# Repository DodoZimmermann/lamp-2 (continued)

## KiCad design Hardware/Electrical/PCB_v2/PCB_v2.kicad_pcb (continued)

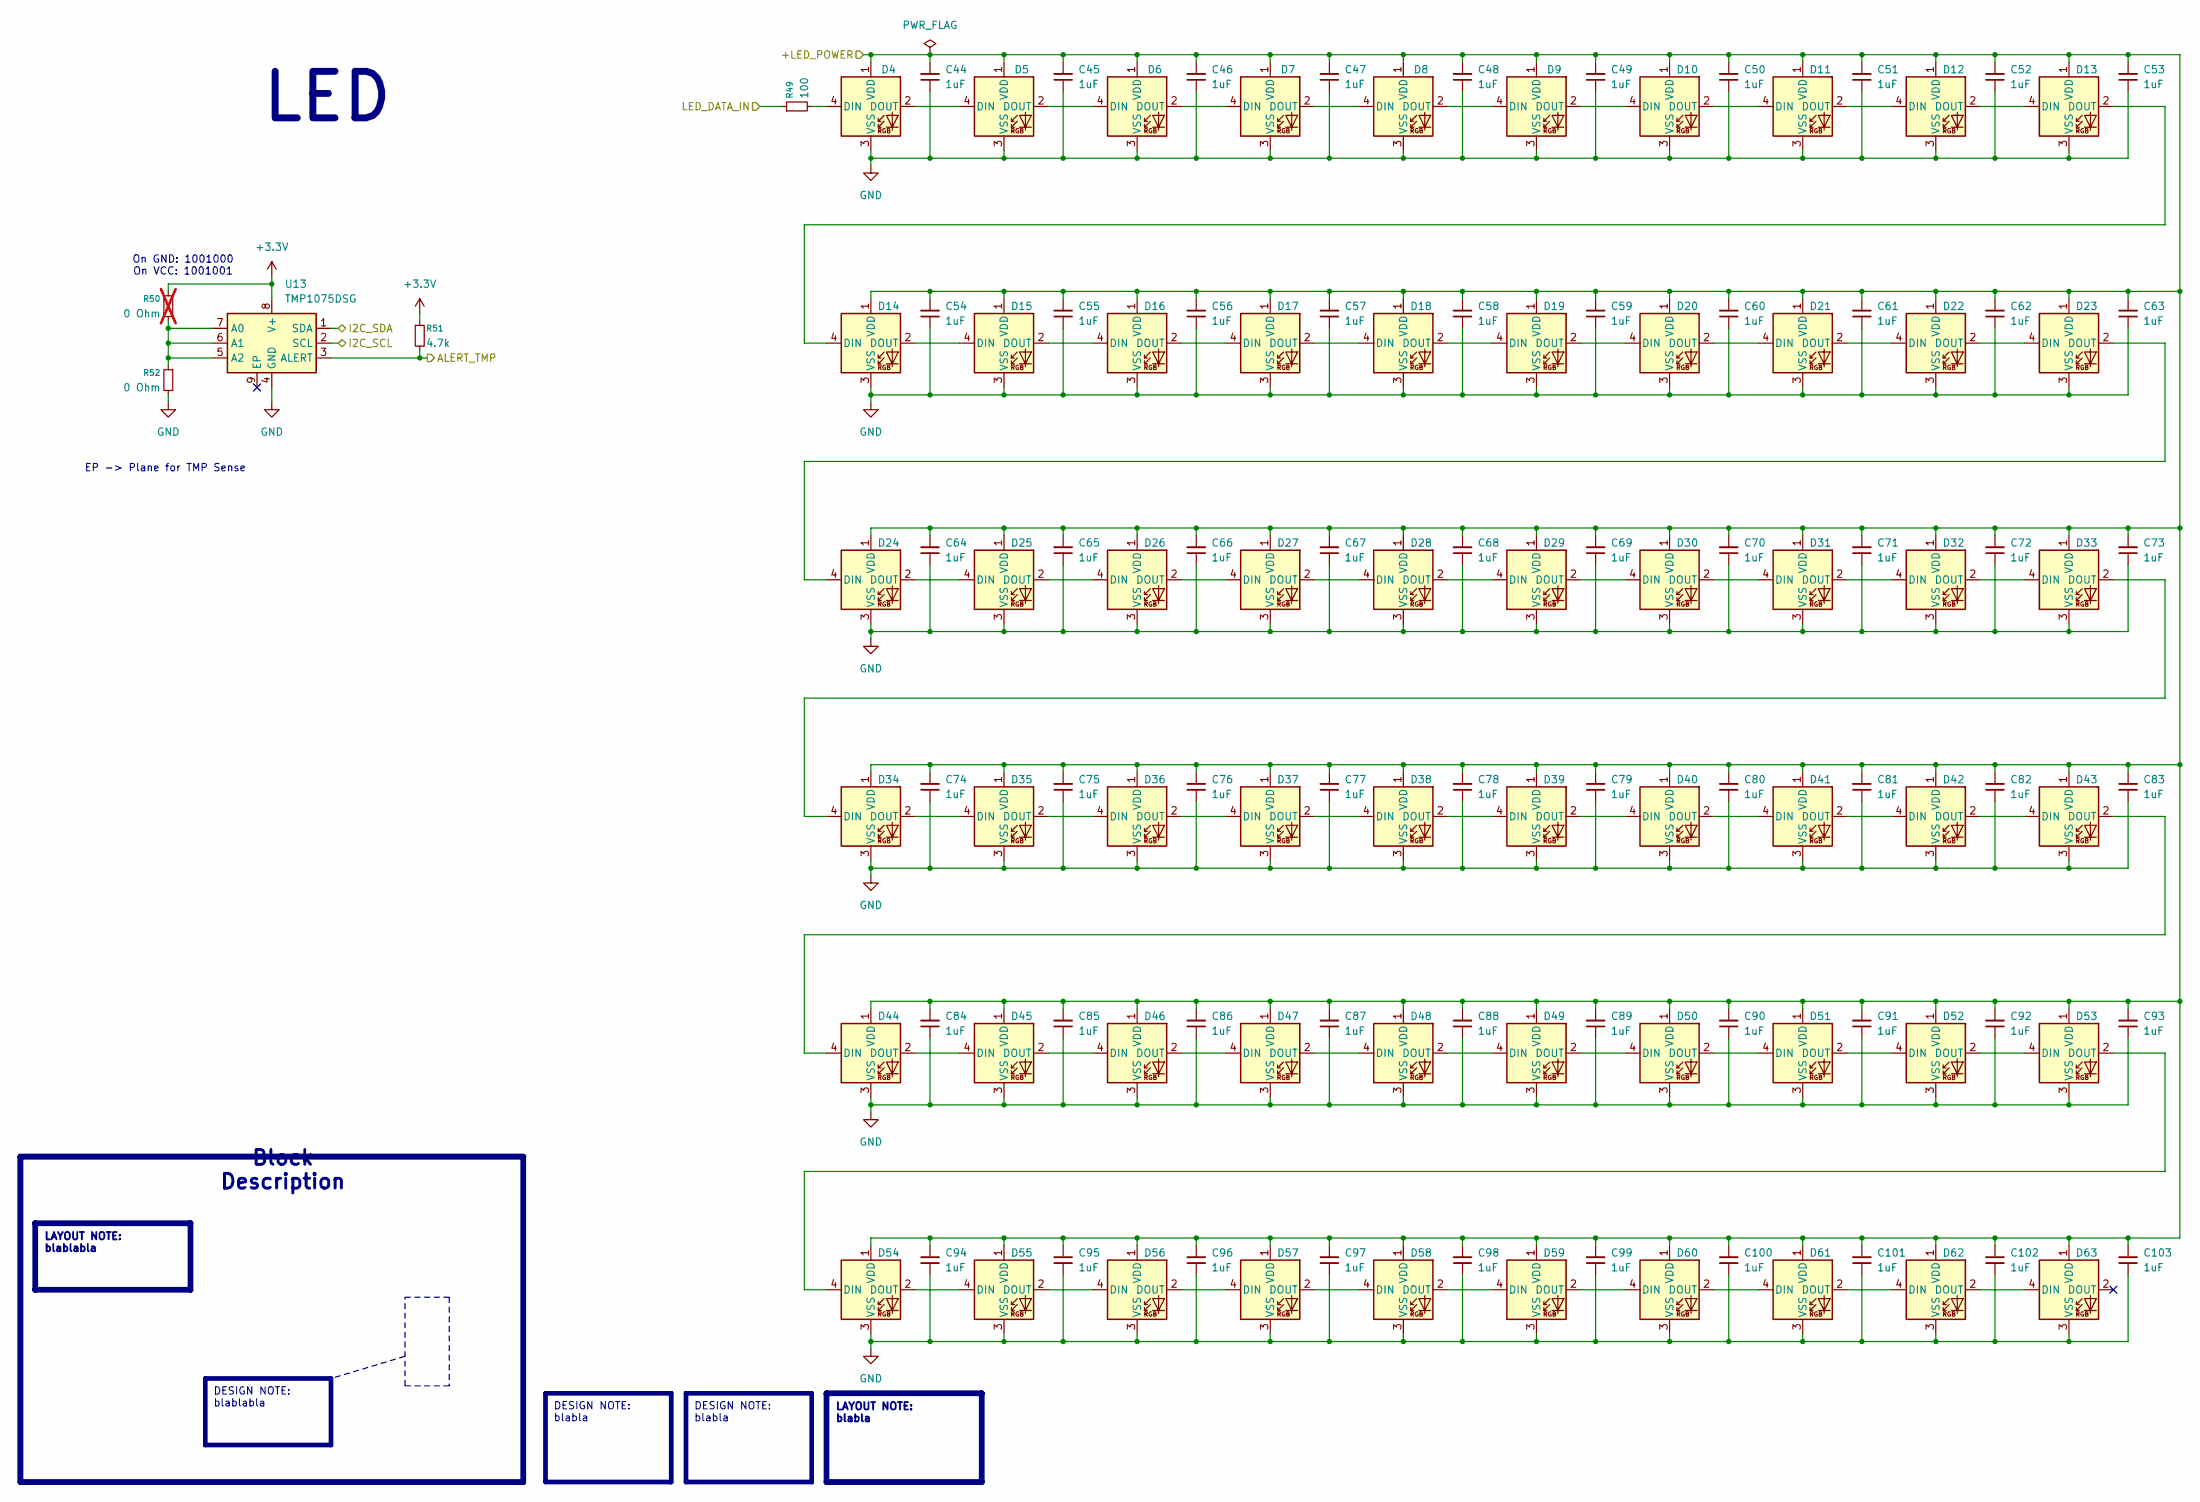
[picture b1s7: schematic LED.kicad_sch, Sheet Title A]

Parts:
C44, C45, C46, C47, C48, C49, C50, C51, C52, C53, C54, C55, C56, C57, C58, C59, C60, C61, C62, C63, C64, C65, C66, C67, C68, C69, C70, C71, C72, C73, C74, C75, C76, C77, C78, C79, C80, C81, C82, C83, C84, C85, C86, C87, C88, C89, C90, C91, C92, C93, C94, C95, C96, C97, C98, C99, C100, C101, C102, C103: 1uF; C_0603_1608Metric; LCSC Part # C15849
D4, D5, D6, D7, D8, D9, D10, D11, D12, D13, D14, D15, D16, D17, D18, D19, D20, D21, D22, D23, D24, D25, D26, D27, D28, D29, D30, D31, D32, D33, D34, D35, D36, D37, D38, D39, D40, D41, D42, D43, D44, D45, D46, D47, D48, D49, D50, D51, D52, D53, D54, D55, D56, D57, D58, D59, D60, D61, D62, D63: WS2812B; LED_WS2812B_PLCC4_5.0x5.0mm_P3.2mm; LCSC Part # C114587
R49: 100; R_0603_1608Metric; LCSC Part # C22775
R50: 0 Ohm; R_0603_1608Metric; not fitted
R51: 4.7k; R_0603_1608Metric; LCSC Part # C23162
R52: 0 Ohm; R_0603_1608Metric; LCSC Part # C21189
U13: TMP1075DSG; WSON-8-1EP_2x2mm_P0.5mm_EP0.9x1.6mm; LCSC Part # C2870250

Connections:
+3.3V: R50.1, R51.1, U13.8 (V+); also elsewhere on the board
+5V: C44.2, C45.2, C46.2, C47.2, C48.2, C49.2, C50.2, C51.2, C52.2, C53.2, C54.2, C55.2, C56.2, C57.2, C58.2, C59.2, C60.2, C61.2, C62.2, C63.2, C64.2, C65.2, C66.2, C67.2, C68.2, C69.2, C70.2, C71.2, C72.2, C73.2, C74.2, C75.2, C76.2, C77.2, C78.2, C79.2, C80.2, C81.2, C82.2, C83.2, C84.2, C85.2, C86.2, C87.2, C88.2, C89.2, C90.2, C91.2, C92.2, C93.2, C94.2, C95.2, C96.2, C97.2, C98.2, C99.2, C100.2, C101.2, C102.2, C103.2, D4.1 (VDD), D5.1 (VDD), D6.1 (VDD), D7.1 (VDD), D8.1 (VDD), D9.1 (VDD), D10.1 (VDD), D11.1 (VDD), D12.1 (VDD), D13.1 (VDD), D14.1 (VDD), D15.1 (VDD), D16.1 (VDD), D17.1 (VDD), D18.1 (VDD), D19.1 (VDD), D20.1 (VDD), D21.1 (VDD), D22.1 (VDD), D23.1 (VDD), D24.1 (VDD), D25.1 (VDD), D26.1 (VDD), D27.1 (VDD), D28.1 (VDD), D29.1 (VDD), D30.1 (VDD), D31.1 (VDD), D32.1 (VDD), D33.1 (VDD), D34.1 (VDD), D35.1 (VDD), D36.1 (VDD), D37.1 (VDD), D38.1 (VDD), D39.1 (VDD), D40.1 (VDD), D41.1 (VDD), D42.1 (VDD), D43.1 (VDD), D44.1 (VDD), D45.1 (VDD), D46.1 (VDD), D47.1 (VDD), D48.1 (VDD), D49.1 (VDD), D50.1 (VDD), D51.1 (VDD), D52.1 (VDD), D53.1 (VDD), D54.1 (VDD), D55.1 (VDD), D56.1 (VDD), D57.1 (VDD), D58.1 (VDD), D59.1 (VDD), D60.1 (VDD), D61.1 (VDD), D62.1 (VDD), D63.1 (VDD); also elsewhere on the board
/Project Architecture/LED/ALERT_TMP: R51.2, U13.3 (ALERT); also elsewhere on the board
/Project Architecture/LED/I2C_SCL: U13.2 (SCL); also elsewhere on the board
/Project Architecture/LED/I2C_SDA: U13.1 (SDA); also elsewhere on the board
/Project Architecture/LED/LED_DATA_IN: R49.1; also elsewhere on the board
GND: C44.1, C45.1, C46.1, C47.1, C48.1, C49.1, C50.1, C51.1, C52.1, C53.1, C54.1, C55.1, C56.1, C57.1, C58.1, C59.1, C60.1, C61.1, C62.1, C63.1, C64.1, C65.1, C66.1, C67.1, C68.1, C69.1, C70.1, C71.1, C72.1, C73.1, C74.1, C75.1, C76.1, C77.1, C78.1, C79.1, C80.1, C81.1, C82.1, C83.1, C84.1, C85.1, C86.1, C87.1, C88.1, C89.1, C90.1, C91.1, C92.1, C93.1, C94.1, C95.1, C96.1, C97.1, C98.1, C99.1, C100.1, C101.1, C102.1, C103.1, D4.3 (VSS), D5.3 (VSS), D6.3 (VSS), D7.3 (VSS), D8.3 (VSS), D9.3 (VSS), D10.3 (VSS), D11.3 (VSS), D12.3 (VSS), D13.3 (VSS), D14.3 (VSS), D15.3 (VSS), D16.3 (VSS), D17.3 (VSS), D18.3 (VSS), D19.3 (VSS), D20.3 (VSS), D21.3 (VSS), D22.3 (VSS), D23.3 (VSS), D24.3 (VSS), D25.3 (VSS), D26.3 (VSS), D27.3 (VSS), D28.3 (VSS), D29.3 (VSS), D30.3 (VSS), D31.3 (VSS), D32.3 (VSS), D33.3 (VSS), D34.3 (VSS), D35.3 (VSS), D36.3 (VSS), D37.3 (VSS), D38.3 (VSS), D39.3 (VSS), D40.3 (VSS), D41.3 (VSS), D42.3 (VSS), D43.3 (VSS), D44.3 (VSS), D45.3 (VSS), D46.3 (VSS), D47.3 (VSS), D48.3 (VSS), D49.3 (VSS), D50.3 (VSS), D51.3 (VSS), D52.3 (VSS), D53.3 (VSS), D54.3 (VSS), D55.3 (VSS), D56.3 (VSS), D57.3 (VSS), D58.3 (VSS), D59.3 (VSS), D60.3 (VSS), D61.3 (VSS), D62.3 (VSS), D63.3 (VSS), R52.2, U13.4 (GND); also elsewhere on the board
unnamed: D4.4 (DIN), R49.2
unnamed: D4.2 (DOUT), D5.4 (DIN)
unnamed: D5.2 (DOUT), D6.4 (DIN)
unnamed: D6.2 (DOUT), D7.4 (DIN)
unnamed: D7.2 (DOUT), D8.4 (DIN)
unnamed: D8.2 (DOUT), D9.4 (DIN)
unnamed: D9.2 (DOUT), D10.4 (DIN)
unnamed: D10.2 (DOUT), D11.4 (DIN)
unnamed: D11.2 (DOUT), D12.4 (DIN)
unnamed: D12.2 (DOUT), D13.4 (DIN)
unnamed: D13.2 (DOUT), D14.4 (DIN)
unnamed: D14.2 (DOUT), D15.4 (DIN)
unnamed: D15.2 (DOUT), D16.4 (DIN)
unnamed: D16.2 (DOUT), D17.4 (DIN)
unnamed: D17.2 (DOUT), D18.4 (DIN)
unnamed: D18.2 (DOUT), D19.4 (DIN)
unnamed: D19.2 (DOUT), D20.4 (DIN)
unnamed: D20.2 (DOUT), D21.4 (DIN)
unnamed: D21.2 (DOUT), D22.4 (DIN)
unnamed: D22.2 (DOUT), D23.4 (DIN)
unnamed: D23.2 (DOUT), D24.4 (DIN)
unnamed: D24.2 (DOUT), D25.4 (DIN)
unnamed: D25.2 (DOUT), D26.4 (DIN)
unnamed: D26.2 (DOUT), D27.4 (DIN)
unnamed: D27.2 (DOUT), D28.4 (DIN)
unnamed: D28.2 (DOUT), D29.4 (DIN)
unnamed: D29.2 (DOUT), D30.4 (DIN)
unnamed: D30.2 (DOUT), D31.4 (DIN)
unnamed: D31.2 (DOUT), D32.4 (DIN)
unnamed: D32.2 (DOUT), D33.4 (DIN)
unnamed: D33.2 (DOUT), D34.4 (DIN)
unnamed: D34.2 (DOUT), D35.4 (DIN)
unnamed: D35.2 (DOUT), D36.4 (DIN)
unnamed: D36.2 (DOUT), D37.4 (DIN)
unnamed: D37.2 (DOUT), D38.4 (DIN)
unnamed: D38.2 (DOUT), D39.4 (DIN)
unnamed: D39.2 (DOUT), D40.4 (DIN)
unnamed: D40.2 (DOUT), D41.4 (DIN)
unnamed: D41.2 (DOUT), D42.4 (DIN)
unnamed: D42.2 (DOUT), D43.4 (DIN)
unnamed: D43.2 (DOUT), D44.4 (DIN)
unnamed: D44.2 (DOUT), D45.4 (DIN)
unnamed: D45.2 (DOUT), D46.4 (DIN)
unnamed: D46.2 (DOUT), D47.4 (DIN)
unnamed: D47.2 (DOUT), D48.4 (DIN)
unnamed: D48.2 (DOUT), D49.4 (DIN)
unnamed: D49.2 (DOUT), D50.4 (DIN)
unnamed: D50.2 (DOUT), D51.4 (DIN)
unnamed: D51.2 (DOUT), D52.4 (DIN)
unnamed: D52.2 (DOUT), D53.4 (DIN)
unnamed: D53.2 (DOUT), D54.4 (DIN)
unnamed: D54.2 (DOUT), D55.4 (DIN)
unnamed: D55.2 (DOUT), D56.4 (DIN)
unnamed: D56.2 (DOUT), D57.4 (DIN)
unnamed: D57.2 (DOUT), D58.4 (DIN)
unnamed: D58.2 (DOUT), D59.4 (DIN)
unnamed: D59.2 (DOUT), D60.4 (DIN)
unnamed: D60.2 (DOUT), D61.4 (DIN)
unnamed: D61.2 (DOUT), D62.4 (DIN)
unnamed: D62.2 (DOUT), D63.4 (DIN)
unnamed: R50.2, R52.1, U13.5 (A2), U13.6 (A1), U13.7 (A0)

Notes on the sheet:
EP -> Plane for TMP Sense
On GND: 1001000 On VCC: 1001001
DESIGN NOTE: blabla
LAYOUT NOTE: blabla
DESIGN NOTE: blablabla
LED
LAYOUT NOTE: blablabla
Block Description

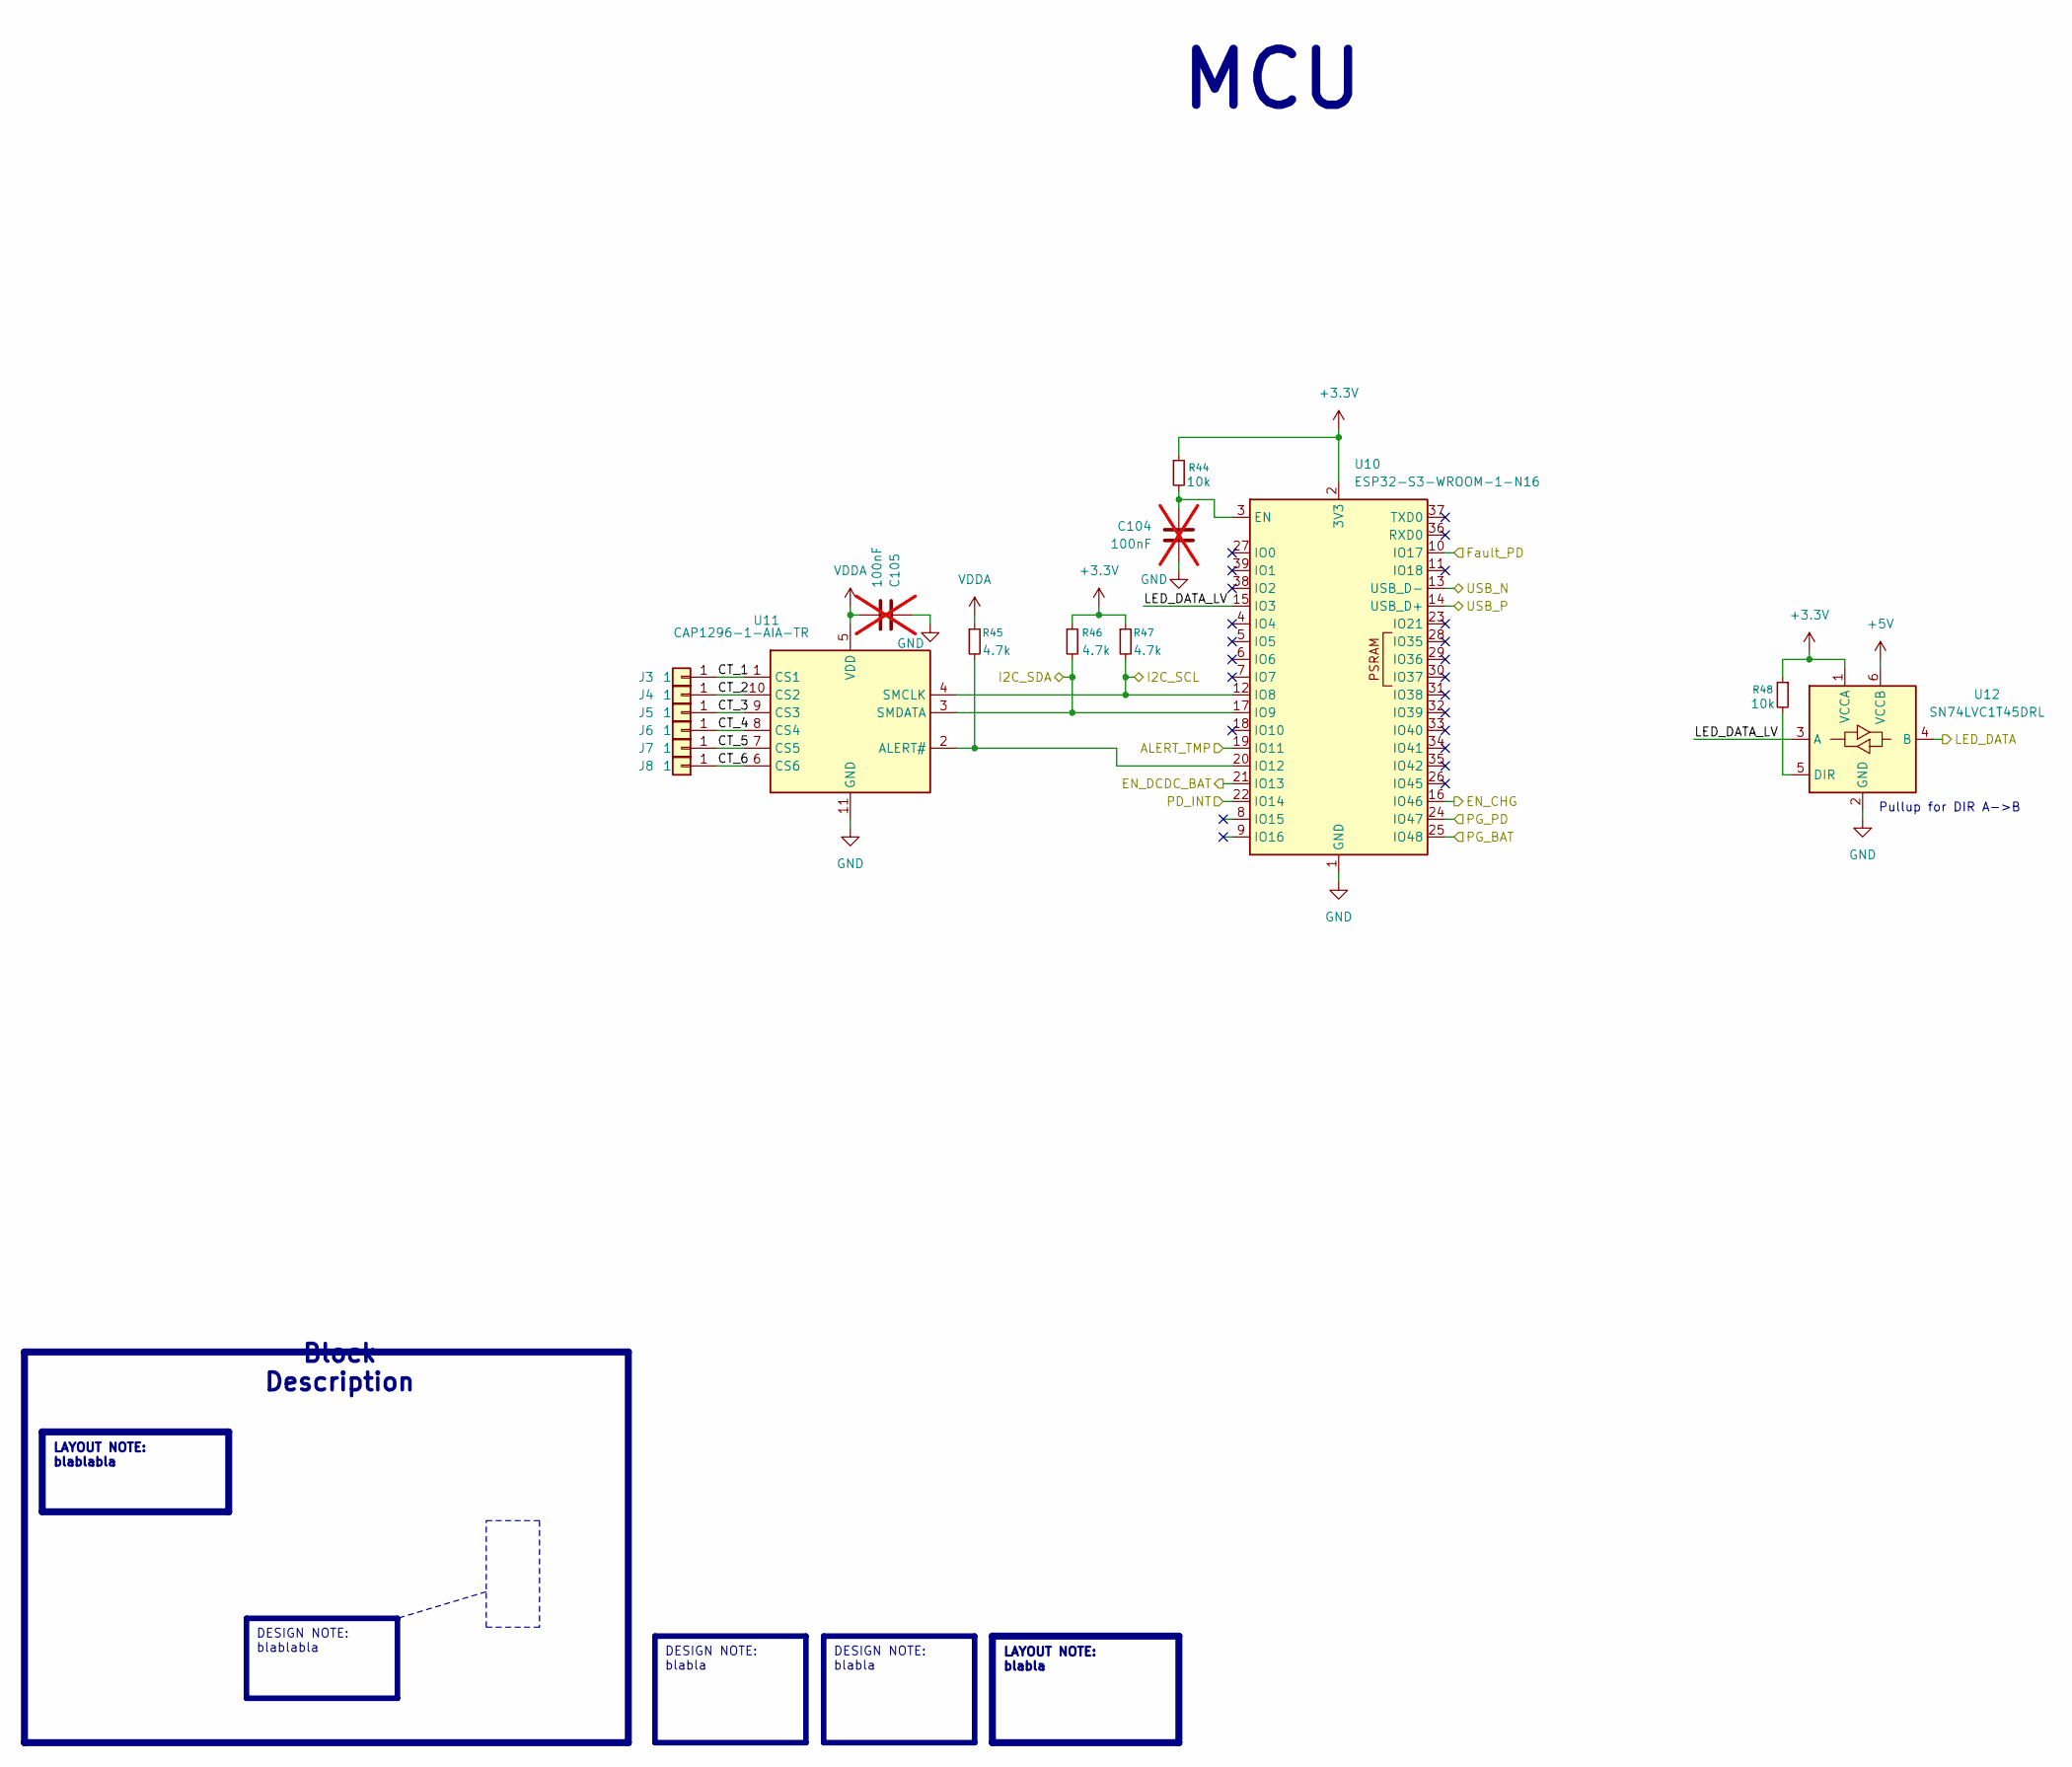
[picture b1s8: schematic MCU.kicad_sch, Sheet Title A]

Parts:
C104, C105: 100nF; C_0603_1608Metric; LCSC Part # C14663; not fitted
J3, J4, J5, J6, J7, J8: 1; JST_XH_B1B-XH-AM_1x01_P2.50mm_Vertical; LCSC Part # C20088533
R44, R48: 10k; R_0603_1608Metric; LCSC Part # C25804
R45, R46, R47: 4.7k; R_0603_1608Metric; LCSC Part # C23162
U10: ESP32-S3-WROOM-1-N16; ESP32-S3-WROOM-1; LCSC Part # C2913199
U11: CAP1296-1-AIA-TR; DFN-10-1EP_3x3mm_P0.5mm_EP1.55x2.48mm; LCSC Part # C2652051
U12: SN74LVC1T45DRL; SOT-563; LCSC Part # C352970

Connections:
+3.3V: R44.1, R46.1, R47.1, R48.1, U10.2 (3V3), U12.1 (VCCA); also elsewhere on the board
+5V: U12.6 (VCCB); also elsewhere on the board
/Project Architecture/Battery/EN_CHG: U10.16 (IO46); also elsewhere on the board
/Project Architecture/LED/ALERT_TMP: U10.19 (IO11); also elsewhere on the board
/Project Architecture/LED/I2C_SCL: R47.2, U10.12 (IO8), U11.4 (SMCLK); also elsewhere on the board
/Project Architecture/LED/I2C_SDA: R46.2, U10.17 (IO9), U11.3 (SMDATA); also elsewhere on the board
/Project Architecture/LED/LED_DATA_IN: U12.4 (B); also elsewhere on the board
/Project Architecture/MCU/CT_1: J3.1 (Pin_1_1), U11.1 (CS1)
/Project Architecture/MCU/CT_2: J4.1 (Pin_1_1), U11.10 (CS2)
/Project Architecture/MCU/CT_3: J5.1 (Pin_1_1), U11.9 (CS3)
/Project Architecture/MCU/CT_4: J6.1 (Pin_1_1), U11.8 (CS4)
/Project Architecture/MCU/CT_5: J7.1 (Pin_1_1), U11.7 (CS5)
/Project Architecture/MCU/CT_6: J8.1 (Pin_1_1), U11.6 (CS6)
/Project Architecture/MCU/EN_DCDC_BAT: U10.21 (IO13); also elsewhere on the board
/Project Architecture/MCU/Fault_PD: U10.10 (IO17); also elsewhere on the board
/Project Architecture/MCU/LED_DATA_LV: U10.15 (IO3), U12.3 (A)
/Project Architecture/MCU/PD_INT: U10.22 (IO14); also elsewhere on the board
/Project Architecture/MCU/PG_BAT: U10.25 (IO48); also elsewhere on the board
/Project Architecture/MCU/PG_PD: U10.24 (IO47); also elsewhere on the board
/Project Architecture/powerdelivery/USB_N: U10.13 (USB_D-); also elsewhere on the board
/Project Architecture/powerdelivery/USB_P: U10.14 (USB_D+); also elsewhere on the board
GND: C104.2, C105.1, U10.1 (GND), U10.40 (GND), U10.41 (GND), U11.11 (GND), U12.2 (GND); also elsewhere on the board
unnamed: C104.1, R44.2, U10.3 (EN)
unnamed: R45.2, U10.20 (IO12), U11.2 (ALERT#)
unnamed: R48.2, U12.5 (DIR)
VDDA: C105.2, R45.1, U11.5 (VDD); also elsewhere on the board

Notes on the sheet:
Pullup for DIR A->B
LAYOUT NOTE: blabla
DESIGN NOTE: blabla
Block Description
LAYOUT NOTE: blablabla
MCU
DESIGN NOTE: blablabla

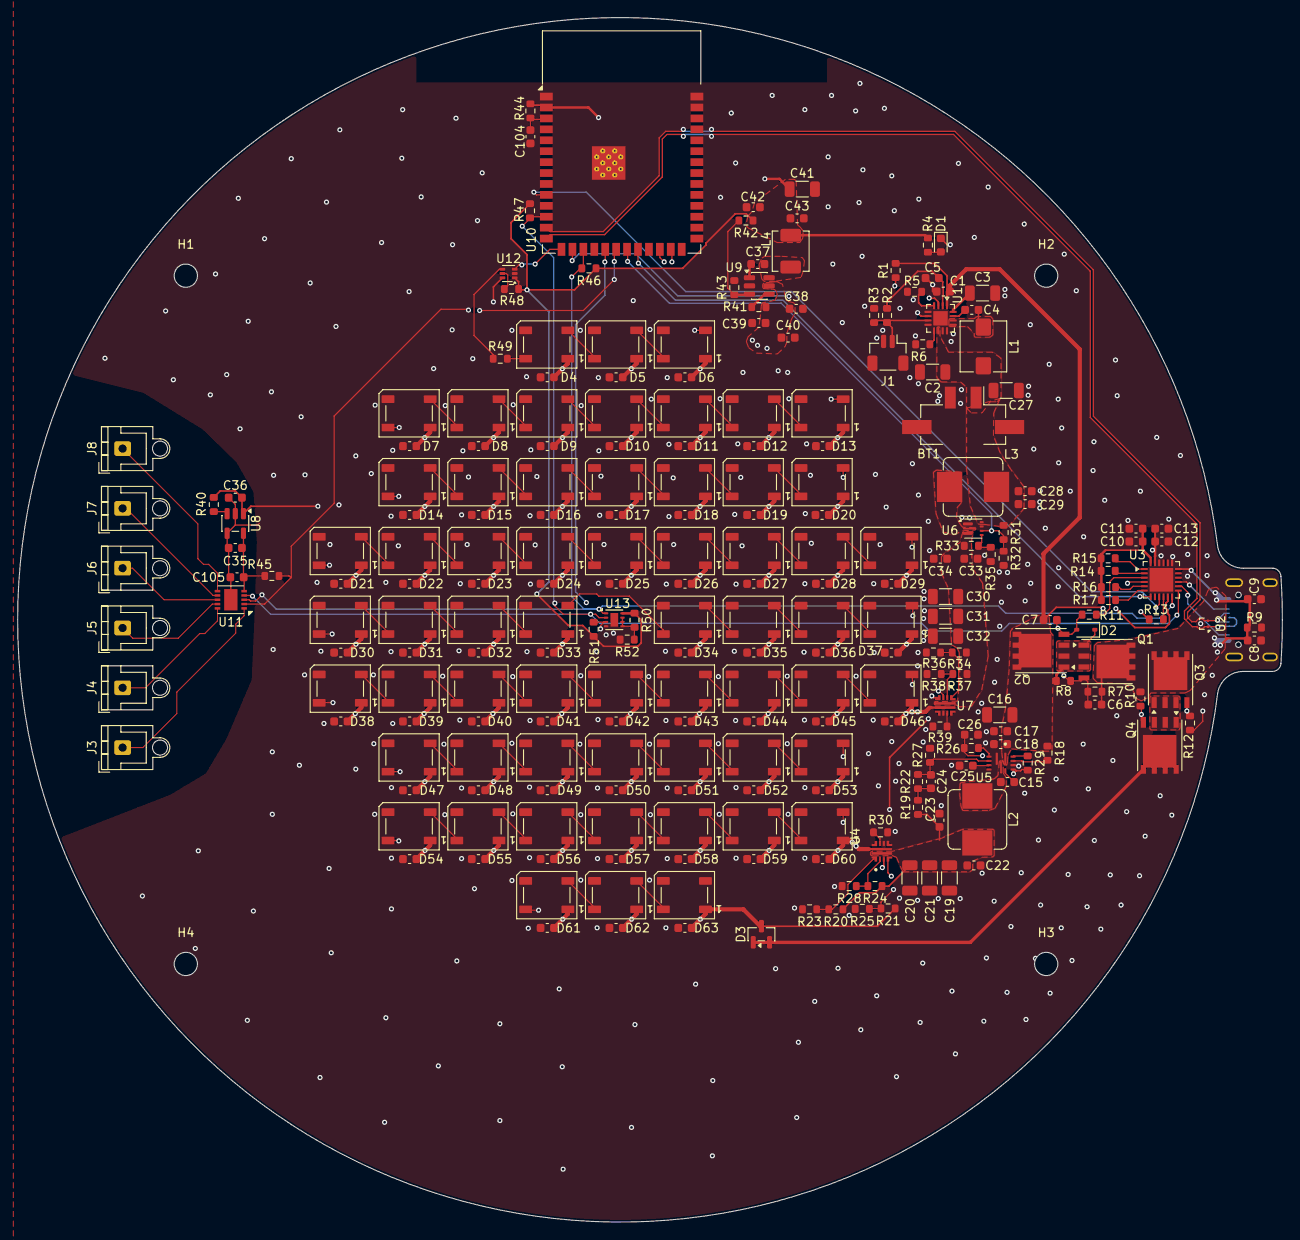
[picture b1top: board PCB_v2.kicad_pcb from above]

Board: 6 copper layers, 147.0 x 140.0 mm, 253 parts (1 on the bottom side), 140 nets.

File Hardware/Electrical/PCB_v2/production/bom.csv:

Designator,Footprint,Quantity,Value,LCSC Part #
BT1,Molex_Micro-Fit_3.0_43650-0224_1x02-1MP_P3.00mm_Vertical,1,Battery_Cell,C122425
"C1, C38, C39, C42, C5",0603,5,2.2uF,C23630
"C10, C104, C105, C13, C15, C18, C23, C29, C34, C37, C40, C43, C8, C9",0603,14,100nF,C14663
"C100, C101, C102, C103, C11, C12, C17, C22, C26, C28, C33, C35, C36, C44, C45, C46, C47, C48, C49, C50, C51, C52, C53, C54, C55, C56, C57, C58, C59, C6, C60, C61, C62, C63, C64, C65, C66, C67, C68, C69, C7, C70, C71, C72, C73, C74, C75, C76, C77, C78, C79, C80, C81, C82, C83, C84, C85, C86, C87, C88, C89, C90, C91, C92, C93, C94, C95, C96, C97, C98, C99",0603,71,1uF,C15849
"C16, C19, C20, C21, C27, C30, C31, C32",1206,8,22uF,C12891
"C2, C3, C41",1206,3,10uF,C13585
C24,0603,1,22p,C1653
C25,0603,1,x,
C4,0603,1,47nF,C1622
D1,0603,1,Orange,C2286
"D10, D11, D12, D13, D14, D15, D16, D17, D18, D19, D20, D21, D22, D23, D24, D25, D26, D27, D28, D29, D30, D31, D32, D33, D34, D35, D36, D37, D38, D39, D4, D40, D41, D42, D43, D44, D45, D46, D47, D48, D49, D5, D50, D51, D52, D53, D54, D55, D56, D57, D58, D59, D6, D60, D61, D62, D63, D7, D8, D9",LED_WS2812B_PLCC4_5.0x5.0mm_P3.2mm,60,WS2812B,C114587
D2,D_SOD-323,1,D_Zener,
D3,SOT-23,1,D_Schottky,C2135
J1,JST_SH_BM02B-SRSS-TB_1x02-1MP_P1.00mm_Vertical,1,10k NTC,C160388
J2,USB_C_Receptacle_GCT_USB4105-xx-A_16P_TopMnt_Horizontal,1,USB_C_Receptacle_USB2.0_16P,
"J3, J4, J5, J6, J7, J8",JST_XH_B1B-XH-AM_1x01_P2.50mm_Vertical,6,1,C20088533
L1,L_Bourns_SRP5030T,1,2.2uH,C2847475
"L2, L3",L_Bourns_SRP7028A_7.3x6.6mm,2,1uH,C2847480
L4,L_Pulse_PA5402,1,4.7uH,C553980
"Q1, Q2, Q3, Q4",PowerPAK_SO-8,4,Q_PMOS,C554002
"R1, R40, R41, R44, R48, R5, R7",0603,7,10k,C25804
"R10, R43, R8",0603,3,49.9k,C23184
"R11, R12",0603,2,1k,C21190
"R13, R45, R46, R47, R51",0603,5,4.7k,C23162
"R14, R15, R16, R17, R52, R6",0603,6,0 Ohm,C21189
R18,0603,1,51k,C23196
R19,0603,1,51,C23197
R2,0603,1,4.32k,C23158
"R20, R34",0603,2,240k,C137765
"R21, R31",0603,2,750k,C137684
R22,0603,1,150k,C22807
"R23, R36",0603,2,62k,C137694
"R24, R37",0603,2,300k,C23024
"R25, R30, R32, R39",0603,4,91k,C23265
"R26, R28, R35, R38",0603,4,100k,C25803
R27,0603,1,20k,C4184
"R29, R50",0603,2,0 Ohm,
R3,0603,1,21k,C137769
R33,0603,1,732k,C246003
R4,0603,1,120,C22765
R42,0603,1,115k,C22783
R49,0603,1,100,C22775
U1,WQFN-16-1EP_3x3mm_P0.5mm_EP1.68x1.68mm,1,BQ25303JRTER,C2842775
U10,ESP32-S3-WROOM-1,1,ESP32-S3-WROOM-1-N16,C2913199
U11,DFN-10-1EP_3x3mm_P0.5mm_EP1.55x2.48mm,1,CAP1296-1-AIA-TR,C2652051
U12,SOT-563,1,SN74LVC1T45DRL,C352970
U13,WSON-8-1EP_2x2mm_P0.5mm_EP0.9x1.6mm,1,TMP1075DSG,C2870250
U2,Texas_DRT-3,1,TPD2EUSB30,C97502
U3,QFN-24-1EP_4x4mm_P0.5mm_EP2.75x2.75mm,1,CYPD3177-24LQ,C2959321
"U4, U7",IC_LM73100RPWR,2,LM73100RPWR,C3210761
U5,VREG_TPS51386RJNR,1,TPS51385,C22418767
U6,Texas_RWU0007A_VQFN-7_2x2mm_P0.5mm,1,TPS61022,C915088
U8,SOT-23-5,1,TLV77333PDBVR,C32445874
U9,SOT-23-6,1,LMR50410,C2841056

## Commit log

2026-01-28 first lamp model
2026-01-28 lamp body with rim added thickness ~2mm, all files updated
2026-01-28 Folder Strucure made
2026-01-28 Schematic, PD and 3.3V DCDC
2026-01-29 battery charger added
2026-03-09 project state at start of school project
2026-03-13 Basic Schematic finished, external connectors missing, no footprints or LCSC numbers yet
2026-03-13 remove temp files
2026-04-02 layout v1 finished but not confirmed yet
2026-04-14 pcb finished but jlcpcb toolkit not working
2026-04-21 manual LED circle done
2026-04-21 removed backup files in PCBv1
2026-04-24 Components placed
2026-04-24 PCB finished, export working
2026-06-07 first Claude Software
2026-06-08 first fully working software, undervoltage not added yet
